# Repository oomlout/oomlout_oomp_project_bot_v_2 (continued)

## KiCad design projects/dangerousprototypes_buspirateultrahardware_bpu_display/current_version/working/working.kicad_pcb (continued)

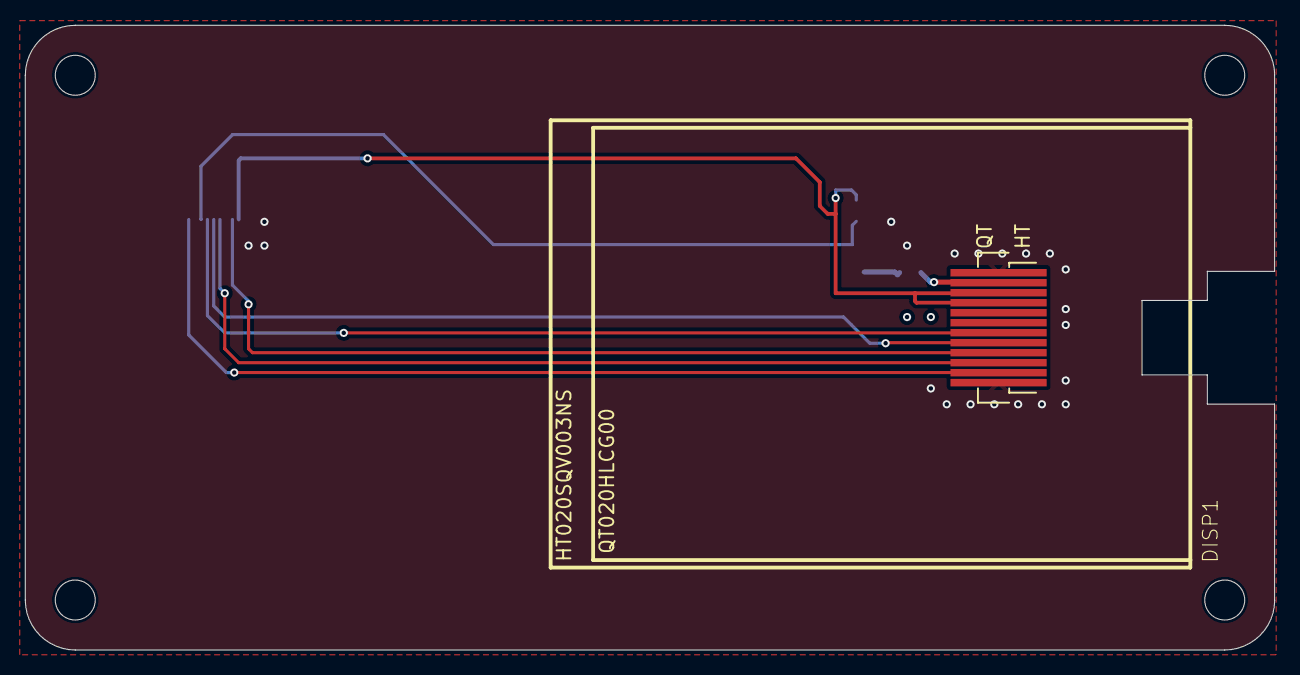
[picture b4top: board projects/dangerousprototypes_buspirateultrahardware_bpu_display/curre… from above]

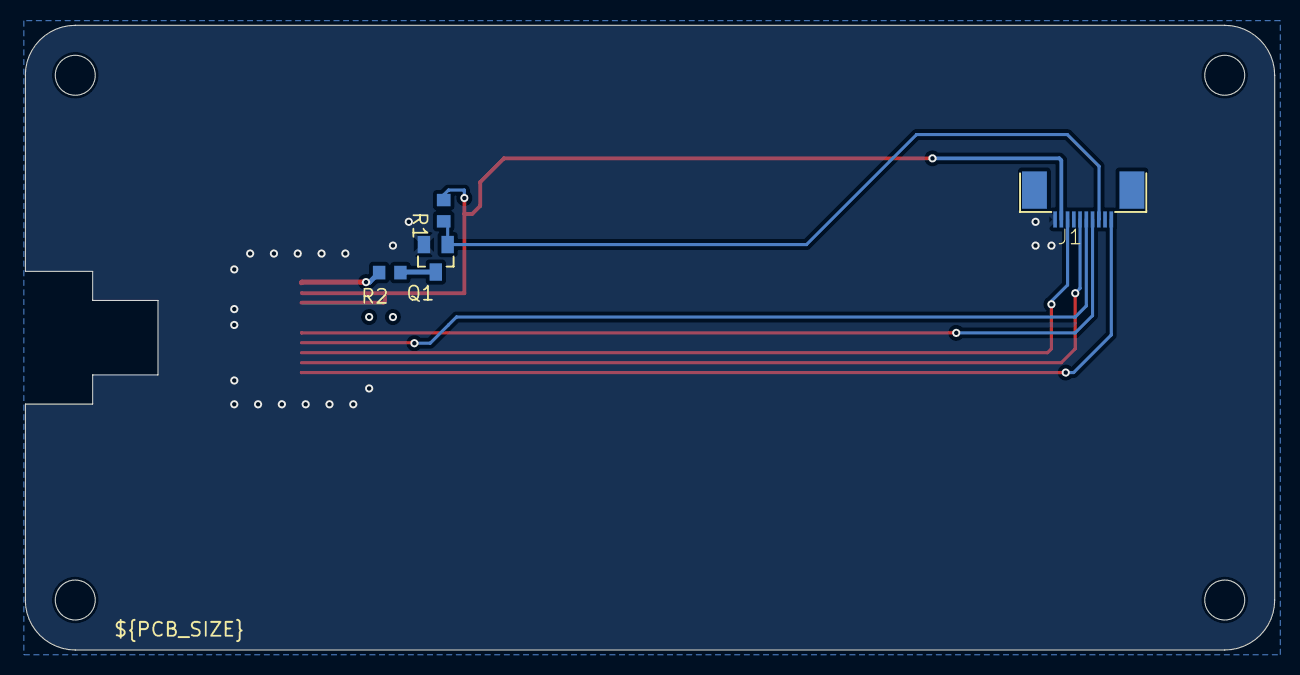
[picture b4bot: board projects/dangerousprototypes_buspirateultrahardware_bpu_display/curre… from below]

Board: 2 copper layers, 100.0 x 50.0 mm, 10 parts (4 on the bottom side), 10 nets.

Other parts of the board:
@HOLE0, @HOLE1, @HOLE2, @HOLE3: (no value)

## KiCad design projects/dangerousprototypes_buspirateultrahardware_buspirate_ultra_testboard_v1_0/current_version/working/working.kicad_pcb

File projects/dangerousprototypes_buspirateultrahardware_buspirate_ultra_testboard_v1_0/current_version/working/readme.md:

# buspirateultrahardware
 
## summary 
* id: dangerousprototypes_buspirateultrahardware_buspirate_ultra_testboard_v1_0
* user: dangerousprototypes
* name: buspirateultrahardware
* board: buspirate_ultra_testboard_v1_0
* repo: https://github.com/DangerousPrototypes/BusPirateUltraHardware

* src_file_repo_sch: 
* src_file_repo_sch_link: https://github.com/DangerousPrototypes/BusPirateUltraHardware/tree/master/
* full details link: https://github.com/oomlout/oomlout_oomp_project_bot_v_2/tree/main/projects/dangerousprototypes_buspirateultrahardware_buspirate_ultra_testboard_v1_0/current_version/working  

## schematic  
  
[schematic (pdf)](working_schematic.pdf) 

## pcb  

[board (pdf)](working.pdf)  

## working_bom
| Id | Designator | Footprint | Quantity | Designation | Supplier and ref |  | None | 
| --- | --- | --- | --- | --- | --- | --- | --- | 
| 1 | LED10,LED1,LED4,LED16,LED15,LED9,LED7,LED8,LED17,LED14,LED5,LED3,LED12,LED11,LED13,LED2,LED6 | LED-805 | 17 |  |  |  | [''] | 
| 2 | PAGE1 | DP_LOGO | 1 | FRAME_DINA4_L |  |  | [''] | 
| 3 | J2 | M1X2 | 1 | CON_HEADER_1X02-PTH |  |  | [''] | 
| 4 | R9,R8,R4,R1,R5,R2,R6,R7,R3 | R603 | 9 | 1k1 |  |  | [''] | 
| 5 | J1 | M1X10_FEMALE_RIGHT_ANGLED_PTH | 1 | CON_HEADER_1X10-RIGHT_ANGLED_PTH |  |  | [''] | 

## bom_schematic
| Ref | Qnty | Value | Cmp name | Footprint | Description | Vendor | DNP | 
| --- | --- | --- | --- | --- | --- | --- | --- | 
| J1 | 1 | CON_HEADER_1X10-RIGHT_ANGLED_PTH | CON_HEADER_1X10-RIGHT_ANGLED_PTH | working:M1X10_FEMALE_RIGHT_ANGLED_PTH |  |  |  | 
| J2 | 1 | CON_HEADER_1X02-PTH | CON_HEADER_1X02-PTH | working:M1X2 |  |  |  | 
| LED1, LED2, LED3, LED4, LED5, LED6, LED7, LED8, LED9, LED10, LED11, LED12, LED13, LED14, LED15, LED16, LED17 | 17 | LED-0805 | LED-0805 | working:LED-805 |  |  |  | 
| PAGE1 | 1 | FRAME_DINA4_L | FRAME_DINA4_L | working:DP_LOGO |  |  |  | 
| R1, R2, R3, R4, R5, R6, R7, R8, R9 | 9 | 1k1 | RESISTOR-0603 | working:R603 |  |  |  |

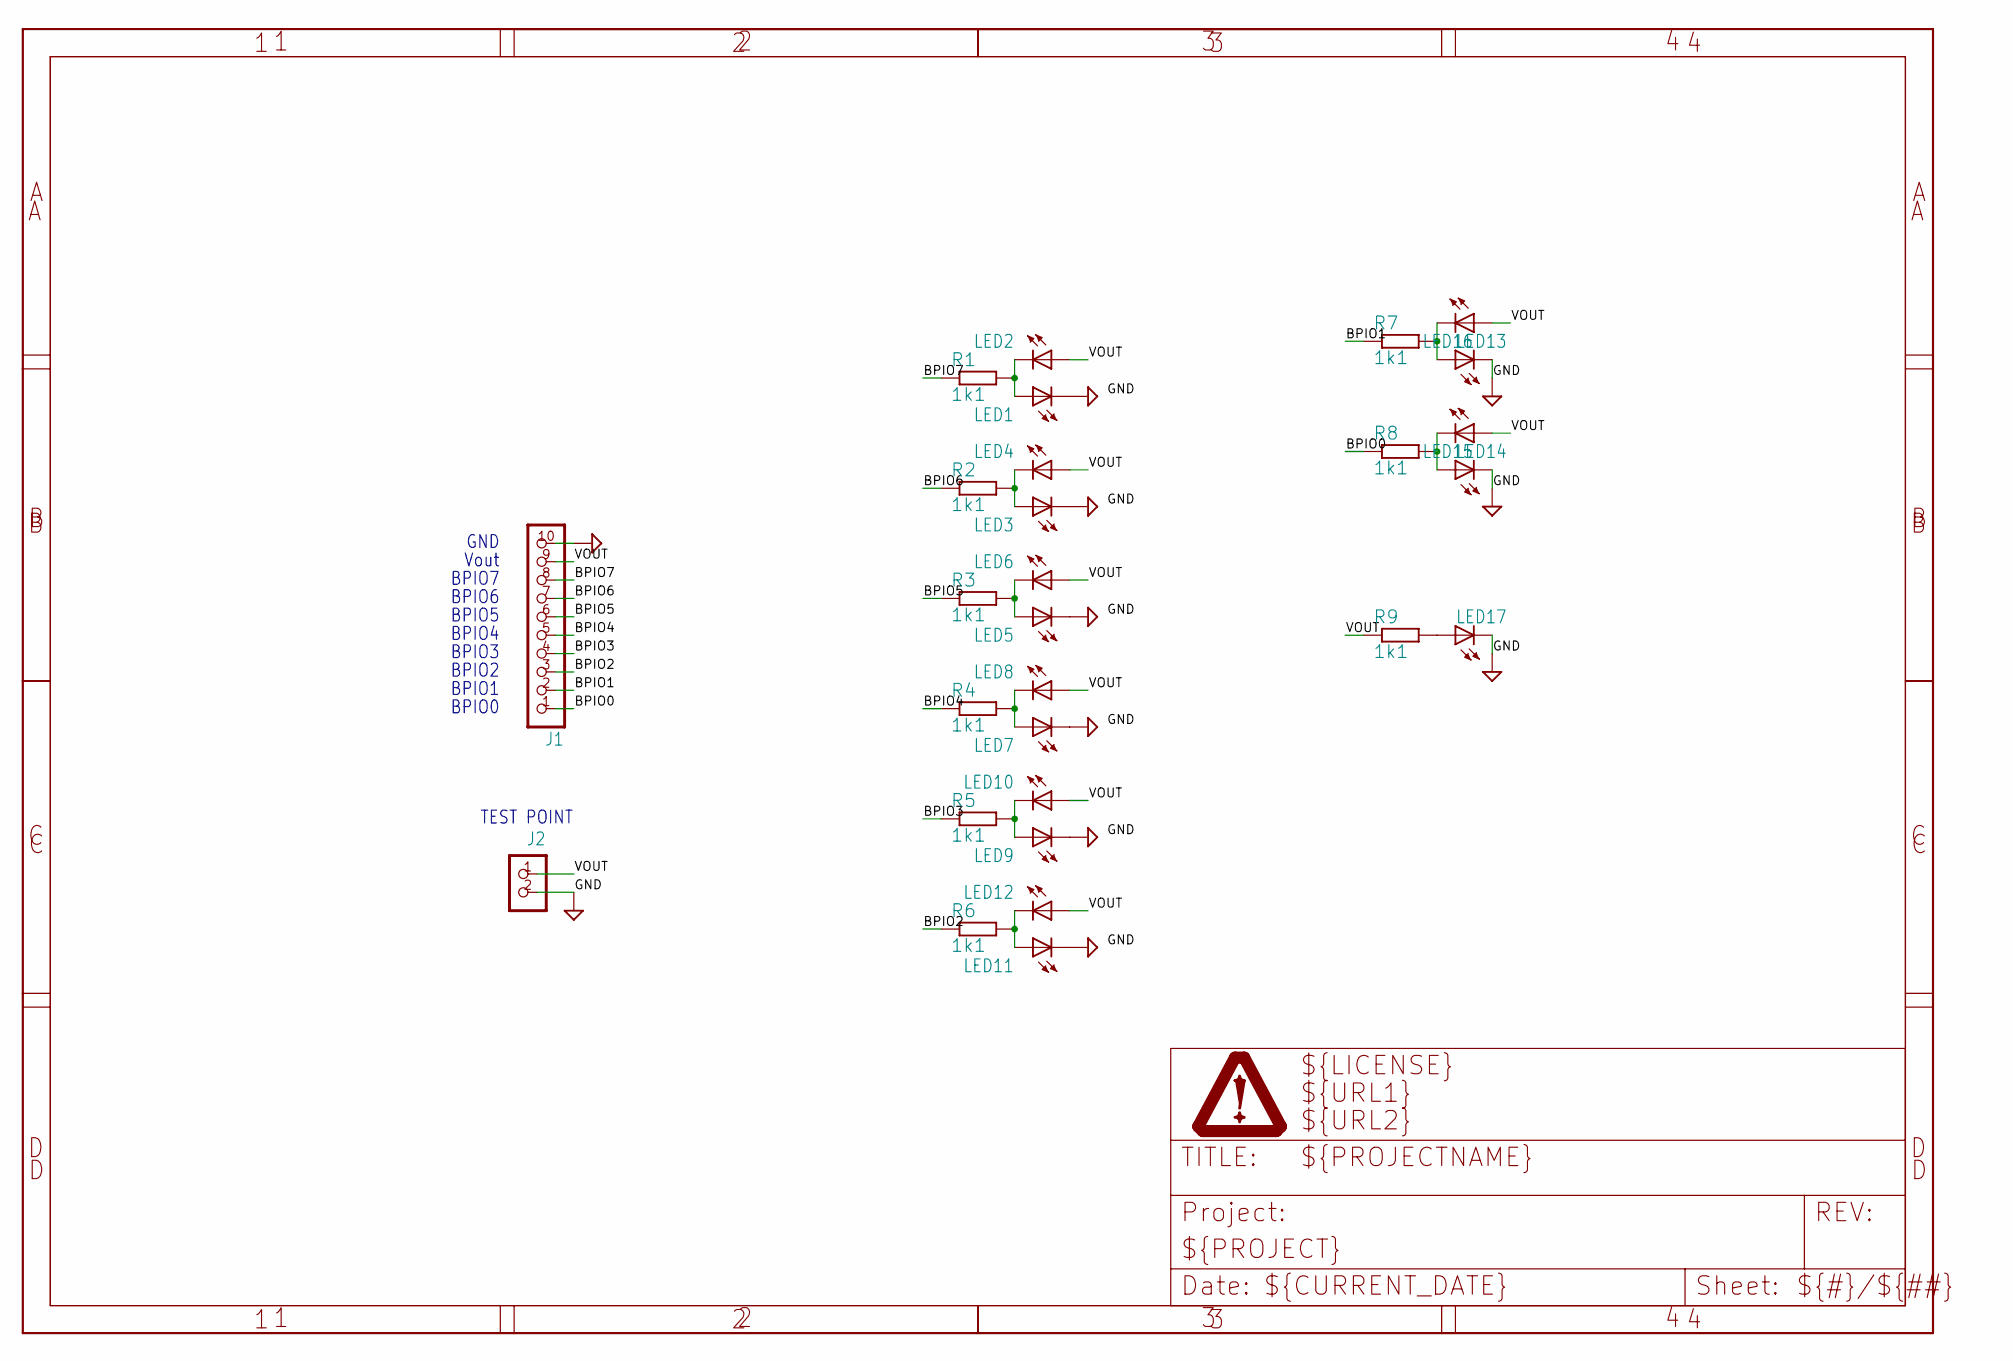
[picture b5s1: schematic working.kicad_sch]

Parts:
J1: CON_HEADER_1X10-RIGHT_ANGLED_PTH; M1X10_FEMALE_RIGHT_ANGLED_PTH
J2: CON_HEADER_1X02-PTH; M1X2
LED1, LED2, LED3, LED4, LED5, LED6, LED7, LED8, LED9, LED10, LED11, LED12, LED13, LED14, LED15, LED16, LED17: LED-0805; LED-805
PAGE1: FRAME_DINA4_L; DP_LOGO
R1, R2, R3, R4, R5, R6, R7, R8, R9: 1k1; R603

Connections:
BPIO0: J1.1, R8.1
BPIO1: J1.2, R7.1
BPIO2: J1.3, R6.1
BPIO3: J1.4, R5.1
BPIO4: J1.5, R4.1
BPIO5: J1.6, R3.1
BPIO6: J1.7, R2.1
BPIO7: J1.8, R1.1
GND: J1.10, J2.2, LED1.C, LED3.C, LED5.C, LED7.C, LED9.C, LED11.C, LED13.C, LED14.C, LED17.C
unnamed: LED1.A, LED2.C, R1.2
unnamed: LED3.A, LED4.C, R2.2
unnamed: LED5.A, LED6.C, R3.2
unnamed: LED7.A, LED8.C, R4.2
unnamed: LED9.A, LED10.C, R5.2
unnamed: LED11.A, LED12.C, R6.2
unnamed: LED14.A, LED15.C, R8.2
unnamed: LED13.A, LED16.C, R7.2
unnamed: LED17.A, R9.2
VOUT: J1.9, J2.1, LED2.A, LED4.A, LED6.A, LED8.A, LED10.A, LED12.A, LED15.A, LED16.A, R9.1

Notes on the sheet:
BPIO0
BPIO3
BPIO4
BPIO6
BPIO2
Vout
BPIO1
GND
BPIO7
TEST POINT
BPIO5

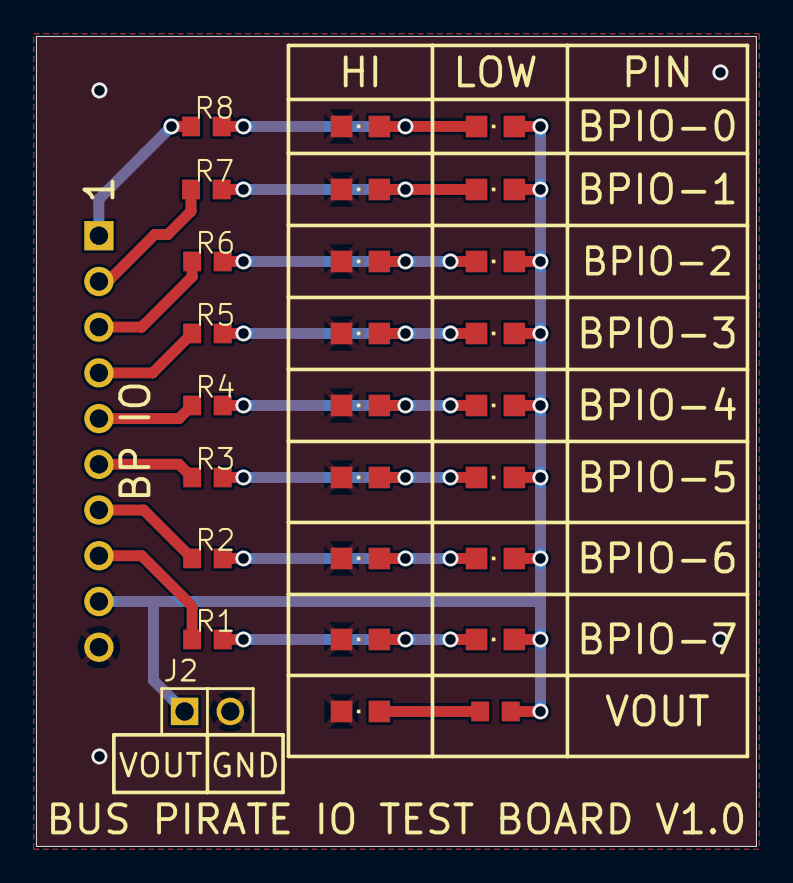
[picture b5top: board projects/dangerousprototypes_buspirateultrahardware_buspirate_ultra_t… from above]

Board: 2 copper layers, 40.0 x 45.0 mm, 29 parts (1 on the bottom side), 19 nets.

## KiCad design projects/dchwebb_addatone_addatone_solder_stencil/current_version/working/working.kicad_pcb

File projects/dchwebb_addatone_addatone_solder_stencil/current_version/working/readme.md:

# addatone
 
## summary 
* id: dchwebb_addatone_addatone_solder_stencil
* user: dchwebb
* name: addatone
* board: addatone_solder_stencil
* repo: https://github.com/dchwebb/Addatone
* src_file_repo_kicad_pcb: Hardware/AddaTone components.kicad_pcb
* src_file_repo_kicad_pcb_link: https://github.com/dchwebb/Addatone/tree/master/Hardware/AddaTone components.kicad_pcb

* src_file_repo_sch: Hardware/AddaTone components.sch
* src_file_repo_sch_link: https://github.com/dchwebb/Addatone/tree/master/Hardware/AddaTone components.sch
* full details link: https://github.com/oomlout/oomlout_oomp_project_bot_v_2/tree/main/projects/dchwebb_addatone_addatone_solder_stencil/current_version/working

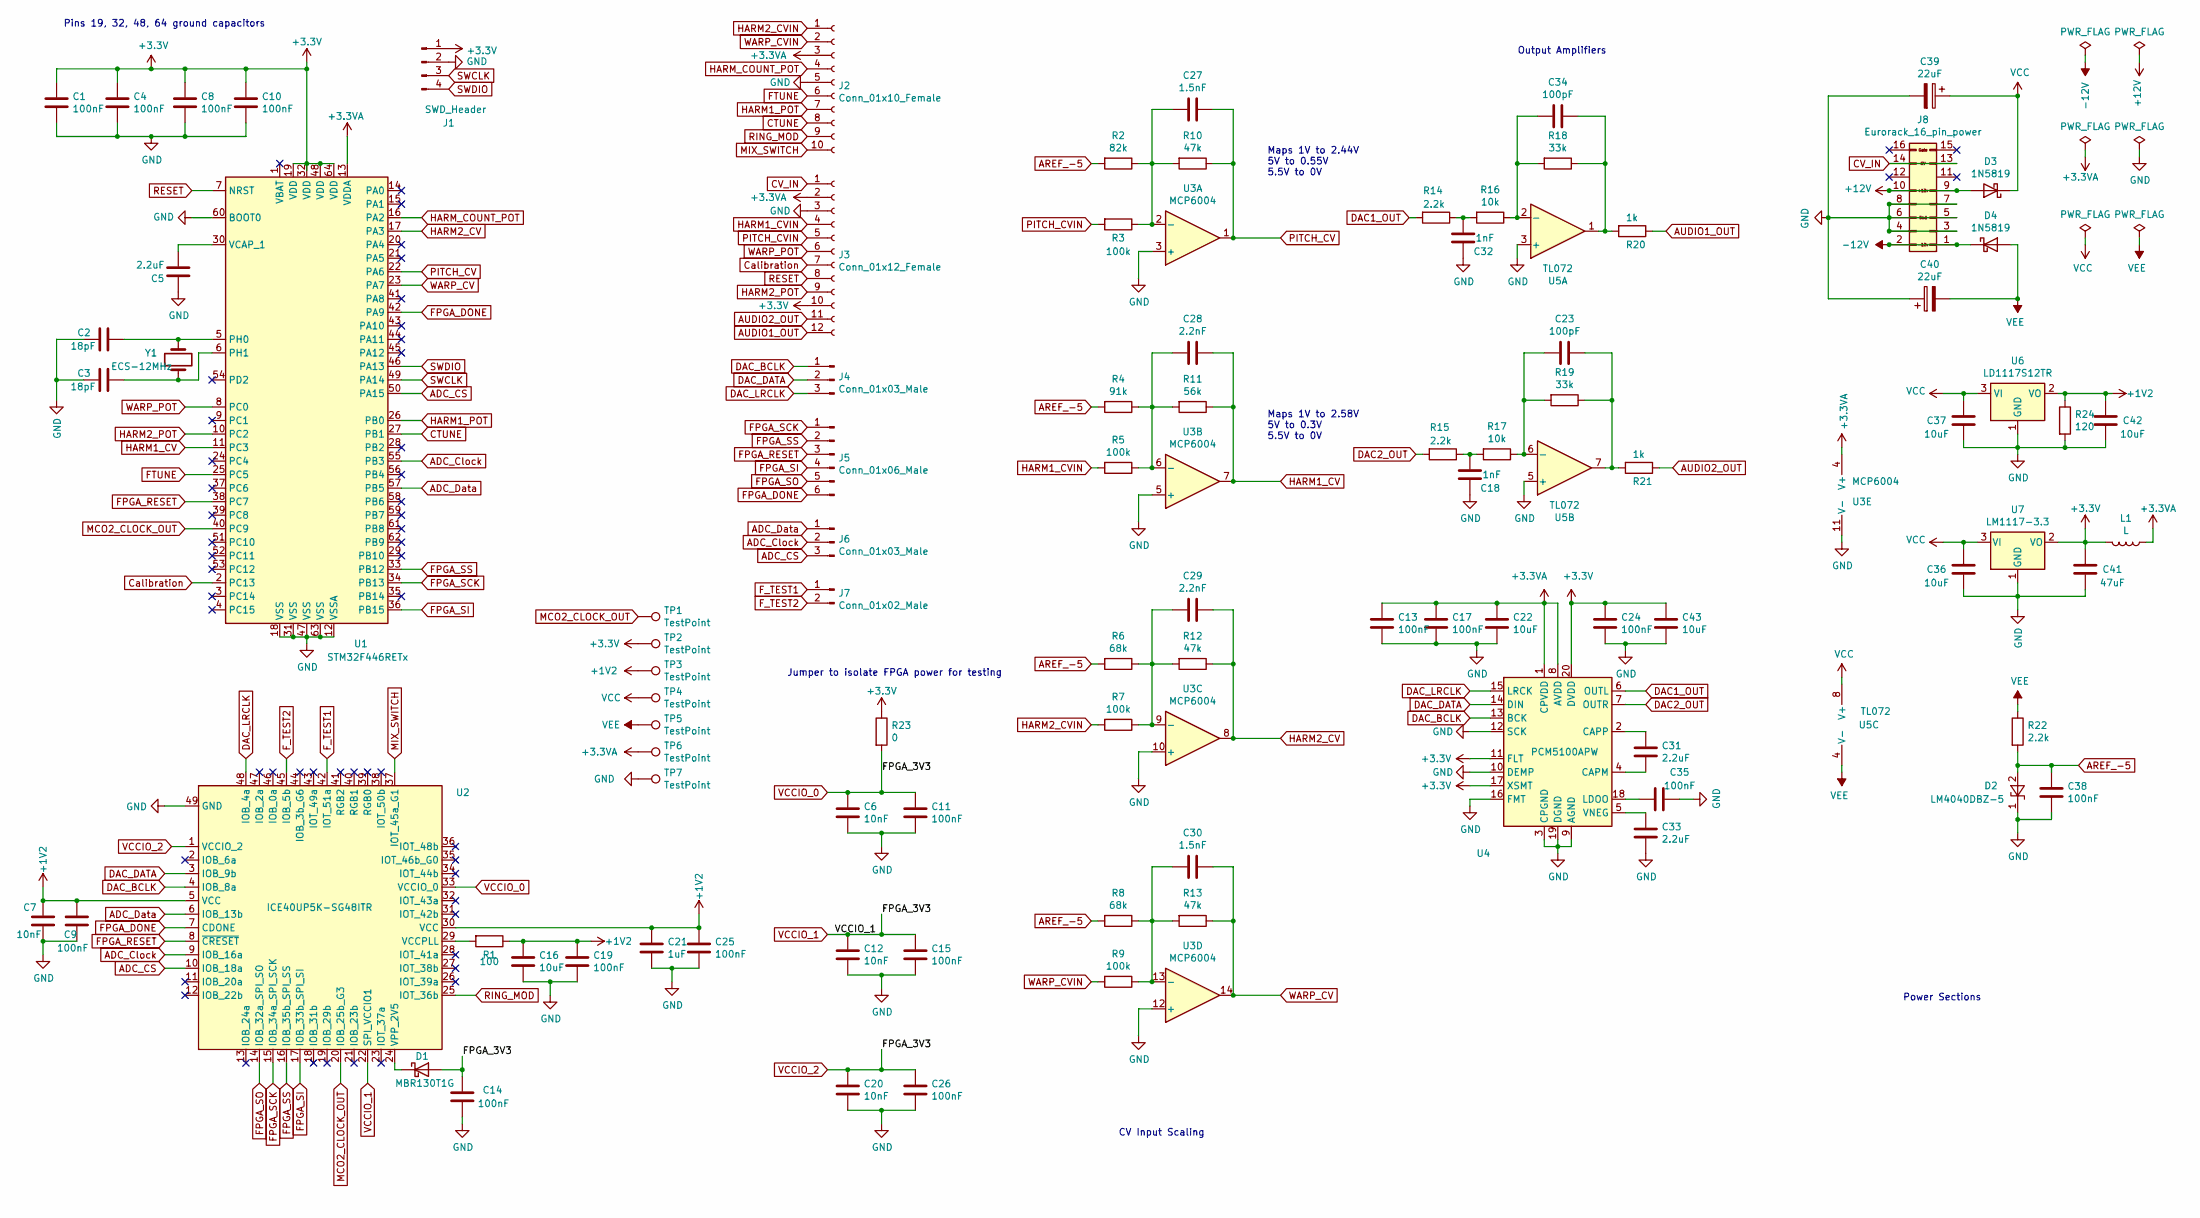
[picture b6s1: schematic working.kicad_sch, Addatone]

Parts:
C1, C4, C9, C15, C35: 100nF; C_0603_HandSoldering
C2, C3: 18pF; C_0805_HandSoldering
C5, C31, C33: 2.2uF; C_0805_HandSoldering
C6, C12, C20: 10nF; C_0805_HandSoldering
C7: 10nF; C_0603_HandSoldering
C8, C10, C11, C13, C14, C17, C19, C24, C25, C26, C38: 100nF; C_0805_HandSoldering
C16, C22, C43: 10uF; C_0805_HandSoldering
C18, C32: 1nF; C_0805_HandSoldering
C21: 1uF; C_0805_HandSoldering
C23, C34: 100pF; C_0805_HandSoldering
C27, C30: 1.5nF; C_0805_HandSoldering
C28, C29: 2.2nF; C_0805_HandSoldering
C36, C37, C42: 10uF; CP_Elec_3x5.3
C39, C40: 22uF; CP_Elec_5x5.3
C41: 47uF; CP_Elec_5x5.3
D1: MBR130T1G; D_SOD-123
D2: LM4040DBZ-5; SOT-23
D3, D4: 1N5819; D_SOD-123
J1: SWD_Header; SWD_header
J2: Conn_01x10_Female; Socket_Strip_Straight_1x10_Pitch2.54mm
J3: Conn_01x12_Female; Socket_Strip_Straight_1x12_Pitch2.54mm
J4, J6: Conn_01x03_Male; Pin_Header_Straight_1x03_Pitch2.54mm
J5: Conn_01x06_Male; Pin_Header_Straight_2x03_Pitch2.54mm
J7: Conn_01x02_Male; Pin_Header_Straight_1x02_Pitch2.54mm
J8: Eurorack_16_pin_power; Eurorack_16_pin_header
L1: L; L_0805_HandSoldering
R1: 100; R_0805_HandSoldering
R2: 82k; R_0805_HandSoldering
R3, R5, R7, R9: 100k; R_0805_HandSoldering
R4: 91k; R_0805_HandSoldering
R6, R8: 68k; R_0805_HandSoldering
R10, R12, R13: 47k; R_0805_HandSoldering
R11: 56k; R_0805_HandSoldering
R14, R15, R22: 2.2k; R_0805_HandSoldering
R16, R17: 10k; R_0805_HandSoldering
R18, R19: 33k; R_0805_HandSoldering
R20, R21: 1k; R_0805_HandSoldering
R23: 0; R_1206
R24: 120; R_0805_HandSoldering
TP1, TP2, TP3, TP4, TP5, TP6: TestPoint; Pin_Header_Straight_1x01_Pitch2.54mm
TP7: TestPoint; Test_Point_Keystone_5010-5014_Multipurpose
U1: STM32F446RETx; LQFP-64_10x10mm_P0.5mm
U2: ICE40UP5K-SG48ITR; ICE40_QFN-48-1EP_7x7mm_Pitch0.5mm
U3: MCP6004; SOIC-14_N
U4: PCM5100APW; SSOP-20_4.4x6.5mm_Pitch0.65mm_Round_Pads
U5: TL072; SOIC-8-N
U6: LD1117S12TR; SOT-223
U7: LM1117-3.3; SOT-223
Y1: ECS-12MHz; Crystal_SMD_0603-2pin_6.0x3.5mm_HandSoldering

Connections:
+1V2: C7.1, C9.1, C16.1, C19.1, C21.1, C25.1, C42.1, R1.1, R24.1, TP3.1, U2.5 (VCC), U2.30 (VCC), U6.2 (VO)
+3.3VA: C13.1, C17.1, C22.1, J2.3, J3.2, L1.1, TP6.1, U1.13 (VDDA), U3.4 (V+), U4.1 (CPVDD), U4.8 (AVDD)
+3V3: C1.1, C4.1, C8.1, C10.1, C24.1, C41.1, C43.1, J1.1, J3.10, L1.2, R23.1, TP2.1, U1.19 (VDD), U1.32 (VDD), U1.48 (VDD), U1.64 (VDD), U4.11 (FLT), U4.17 (XSMT), U4.20 (DVDD), U7.2 (VO)
+12V: D3.2 (A), J8.9, J8.10
-12V: D4.1 (K), J8.1, J8.2
ADC_CS: J6.3, U1.50 (PA15), U2.10 (IOB_18a)
ADC_Clock: J6.2, U1.55 (PB3), U2.9 (IOB_16a)
ADC_Data: J6.1, U1.57 (PB5), U2.6 (IOB_13b)
AREF_-5: C38.1, D2.2 (A), R2.2, R4.2, R6.2, R8.2, R22.2
AUDIO1_OUT: J3.12, R20.1
AUDIO2_OUT: J3.11, R21.1
CTUNE: J2.8, U1.27 (PB1)
CV_IN: J3.1, J8.13, J8.14
Calibration: J3.7, U1.2 (PC13)
DAC1_OUT: R14.2, U4.6 (OUTL)
DAC2_OUT: R15.2, U4.7 (OUTR)
DAC_BCLK: J4.1, U2.4 (IOB_8a), U4.13 (BCK)
DAC_DATA: J4.2, U2.3 (IOB_9b), U4.14 (DIN)
DAC_LRCLK: J4.3, U2.48 (IOB_4a), U4.15 (LRCK)
FPGA_DONE: J5.6, U1.42 (PA9), U2.7 (CDONE)
FPGA_RESET: J5.3, U1.38 (PC7), U2.8 (~CRESET)
FPGA_SCK: J5.1, U1.34 (PB13), U2.15 (IOB_34a_SPI_SCK)
FPGA_SI: J5.4, U1.36 (PB15), U2.17 (IOB_33b_SPI_SI)
FPGA_SO: J5.5, U2.14 (IOB_32a_SPI_SO)
FPGA_SS: J5.2, U1.33 (PB12), U2.16 (IOB_35b_SPI_SS)
FTUNE: J2.6, U1.25 (PC5)
F_TEST1: J7.1, U2.42 (IOT_51a)
F_TEST2: J7.2, U2.45 (IOB_5b)
GND: C1.2, C2.2, C3.2, C4.2, C5.1, C6.2, C7.2, C8.2, C9.2, C10.2, C11.2, C12.2, C13.2, C14.1, C15.2, C16.2, C17.2, C18.1, C19.2, C20.2, C21.2, C22.2, C24.2, C25.2, C26.2, C32.1, C33.2, C35.1, C36.2, C37.2, C38.2, C39.2, C40.1, C41.2, C42.2, C43.2, D2.1 (K), J1.2, J2.5, J3.3, J8.3, J8.4, J8.5, J8.6, J8.7, J8.8, R24.2, TP7.1, U1.12 (VSSA), U1.18 (VSS), U1.31 (VSS), U1.47 (VSS), U1.60 (BOOT0), U1.63 (VSS), U2.49 (GND), U3.3 (+), U3.5 (+), U3.10 (+), U3.11 (V-), U3.12 (+), U4.3 (CPGND), U4.9 (AGND), U4.10 (DEMP), U4.12 (SCK), U4.16 (FMT), U4.19 (DGND), U5.3 (+), U5.5 (+), U6.1 (GND), U7.1 (GND)
HARM1_CV: C28.2, R11.1, U1.11 (PC3), U3.7
HARM1_CVIN: J3.4, R5.2
HARM1_POT: J2.7, U1.26 (PB0)
HARM2_CV: C29.2, R12.1, U1.17 (PA3), U3.8
HARM2_CVIN: J2.1, R7.2
HARM2_POT: J3.9, U1.10 (PC2)
HARM_COUNT_POT: J2.4, U1.16 (PA2)
MCO2_CLOCK_OUT: TP1.1, U1.40 (PC9), U2.20 (IOB_25b_G3)
MIX_SWITCH: J2.10, U2.37 (IOT_45a_G1)
unnamed: C2.1, U1.5 (PH0), Y1.2
unnamed: C3.1, U1.6 (PH1), Y1.1
unnamed: C5.2, U1.30 (VCAP_1)
unnamed: C18.2, R15.1, R17.2
unnamed: C23.1, R17.1, R19.2, U5.6 (-)
unnamed: C23.2, R19.1, R21.2, U5.7
unnamed: C27.1, R2.1, R3.1, R10.2, U3.2 (-)
unnamed: C28.1, R4.1, R5.1, R11.2, U3.6 (-)
unnamed: C29.1, R6.1, R7.1, R12.2, U3.9 (-)
unnamed: C30.1, R8.1, R9.1, R13.2, U3.13 (-)
unnamed: C31.1, U4.2 (CAPP)
unnamed: C31.2, U4.4 (CAPM)
unnamed: C32.2, R14.1, R16.2
unnamed: C33.1, U4.5 (VNEG)
unnamed: C34.1, R16.1, R18.2, U5.2 (-)
unnamed: C34.2, R18.1, R20.2, U5.1
unnamed: C35.2, U4.18 (LDOO)
unnamed: D1.1 (K), U2.24 (VPP_2V5)
unnamed: R1.2, U2.29 (VCCPLL)
PITCH_CV: C27.2, R10.1, U1.22 (PA6), U3.1
PITCH_CVIN: J3.5, R3.2
RESET: J3.8, U1.7 (NRST)
RING_MOD: J2.9, U2.25 (IOT_36b)
SWCLK: J1.3, U1.49 (PA14)
SWDIO: J1.4, U1.46 (PA13)
VCC: C36.1, C37.1, C39.1, D3.1 (K), TP4.1, U5.8 (V+), U6.3 (VI), U7.3 (VI)
VCCIO_0: C6.1, C11.1, C12.1, C14.2, C15.1, C20.1, C26.1, D1.2 (A), R23.2, U2.1 (VCCIO_2), U2.22 (SPI_VCCIO1), U2.33 (VCCIO_0)
VEE: C40.2, D4.2 (A), R22.1, TP5.1, U5.4 (V-)
WARP_CV: C30.2, R13.1, U1.23 (PA7), U3.14
WARP_CVIN: J2.2, R9.2
WARP_POT: J3.6, U1.8 (PC0)

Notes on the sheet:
Power Sections
Jumper to isolate FPGA power for testing
Maps 1V to 2.58V 5V to 0.3V 5.5V to 0V
Output Amplifiers
CV Input Scaling
Maps 1V to 2.44V 5V to 0.55V 5.5V to 0V
Pins 19, 32, 48, 64 ground capacitors

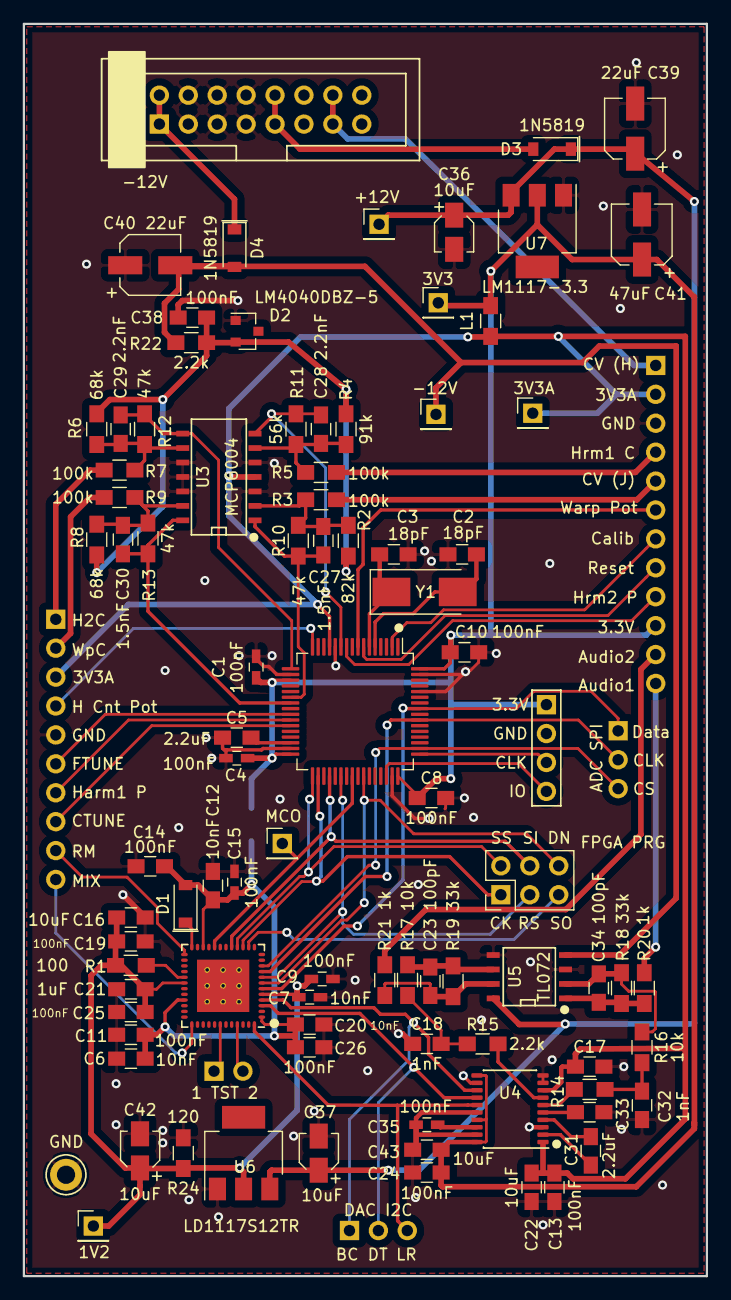
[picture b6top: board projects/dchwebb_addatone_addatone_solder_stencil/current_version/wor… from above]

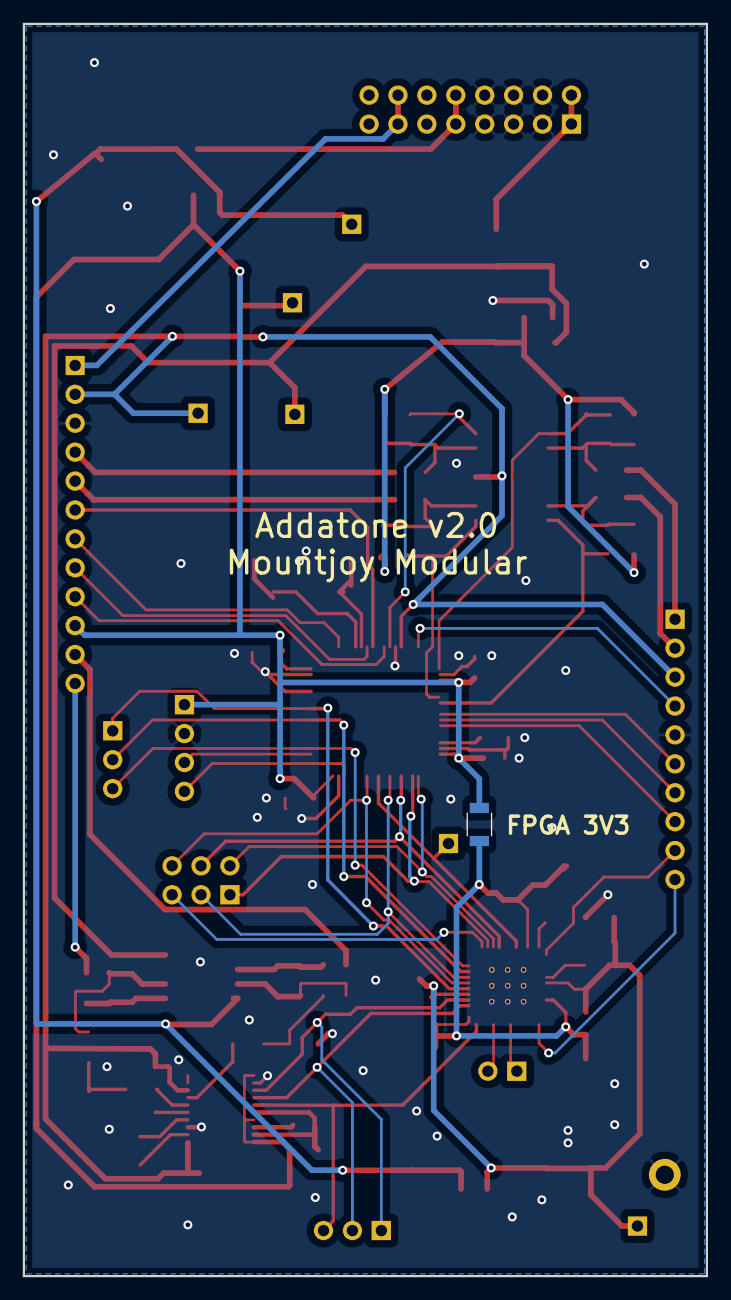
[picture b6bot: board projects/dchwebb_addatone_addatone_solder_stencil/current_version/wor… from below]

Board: 2 copper layers, 60.0 x 110.0 mm, 95 parts (3 on the bottom side), 69 nets.
